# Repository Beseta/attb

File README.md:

# AT-Tiny Bootloader

AT-Tiny 85 bootloader board. Schematic designed by [INTION](https://www.youtube.com/@INTION1). PCB board designed by me.

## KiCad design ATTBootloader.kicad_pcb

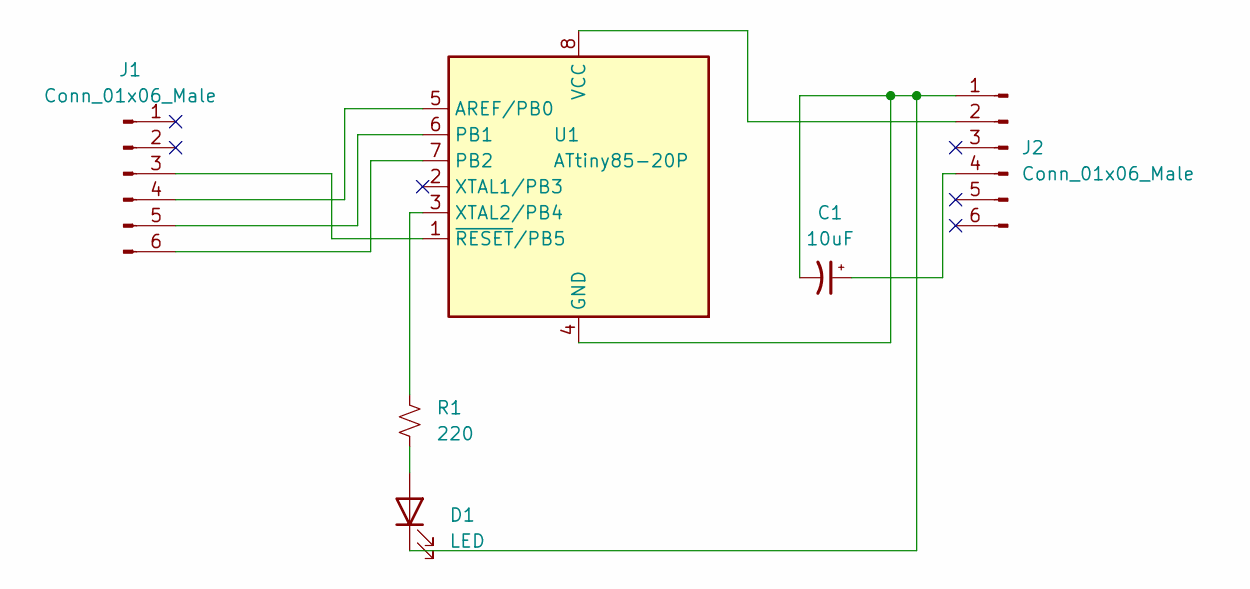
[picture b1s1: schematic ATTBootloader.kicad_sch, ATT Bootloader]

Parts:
C1: 10uF; CP_Radial_D5.0mm_P2.50mm
D1: LED; LED_D1.8mm_W3.3mm_H2.4mm
J1, J2: Conn_01x06_Male; PinHeader_1x06_P2.54mm_Vertical
R1: 220; R_Axial_DIN0204_L3.6mm_D1.6mm_P5.08mm_Horizontal
U1: ATtiny85-20P; DIP-8_W7.62mm

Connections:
unnamed: C1.1, J2.4
unnamed: C1.2, D1.1 (K), J2.1, U1.4 (GND)
unnamed: D1.2 (A), R1.2
unnamed: J1.3, U1.1 (~RESET/PB5)
unnamed: J1.4, U1.5 (AREF/PB0)
unnamed: J1.5, U1.6 (PB1)
unnamed: J1.6, U1.7 (PB2)
unnamed: J2.2, U1.8 (VCC)
unnamed: R1.1, U1.3 (XTAL2/PB4)

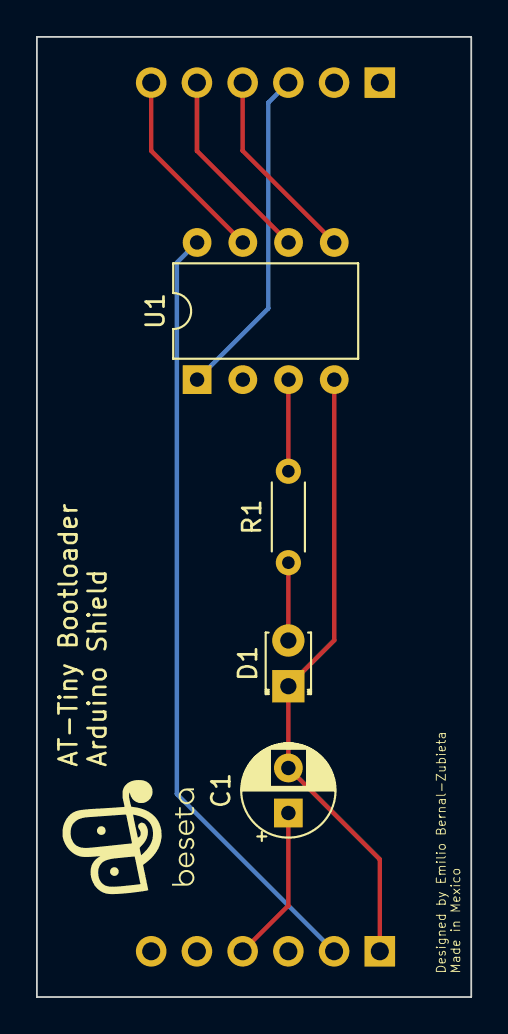
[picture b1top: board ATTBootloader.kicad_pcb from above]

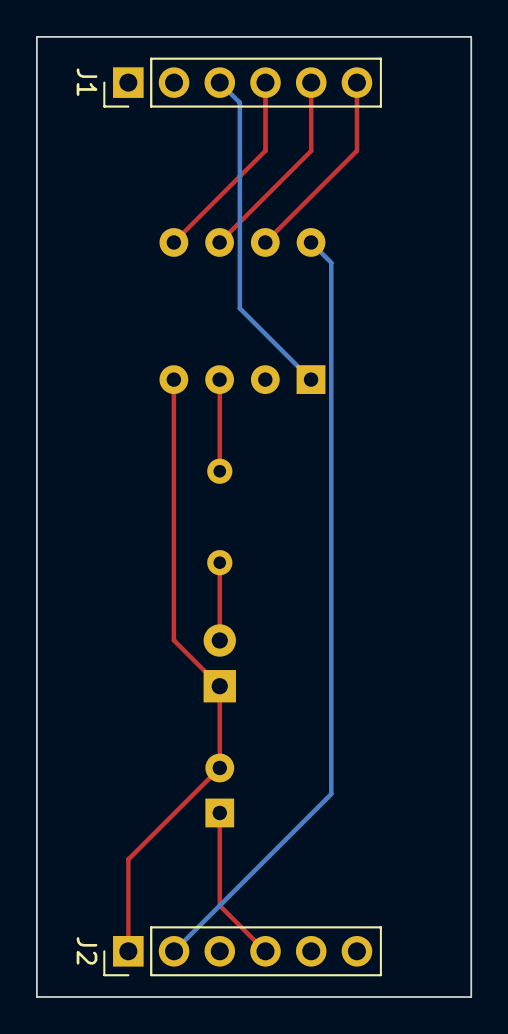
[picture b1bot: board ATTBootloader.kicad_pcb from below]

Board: 2 copper layers, 24.1 x 53.3 mm, 6 parts (2 on the bottom side), 9 nets.

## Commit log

2023-04-25 added images
